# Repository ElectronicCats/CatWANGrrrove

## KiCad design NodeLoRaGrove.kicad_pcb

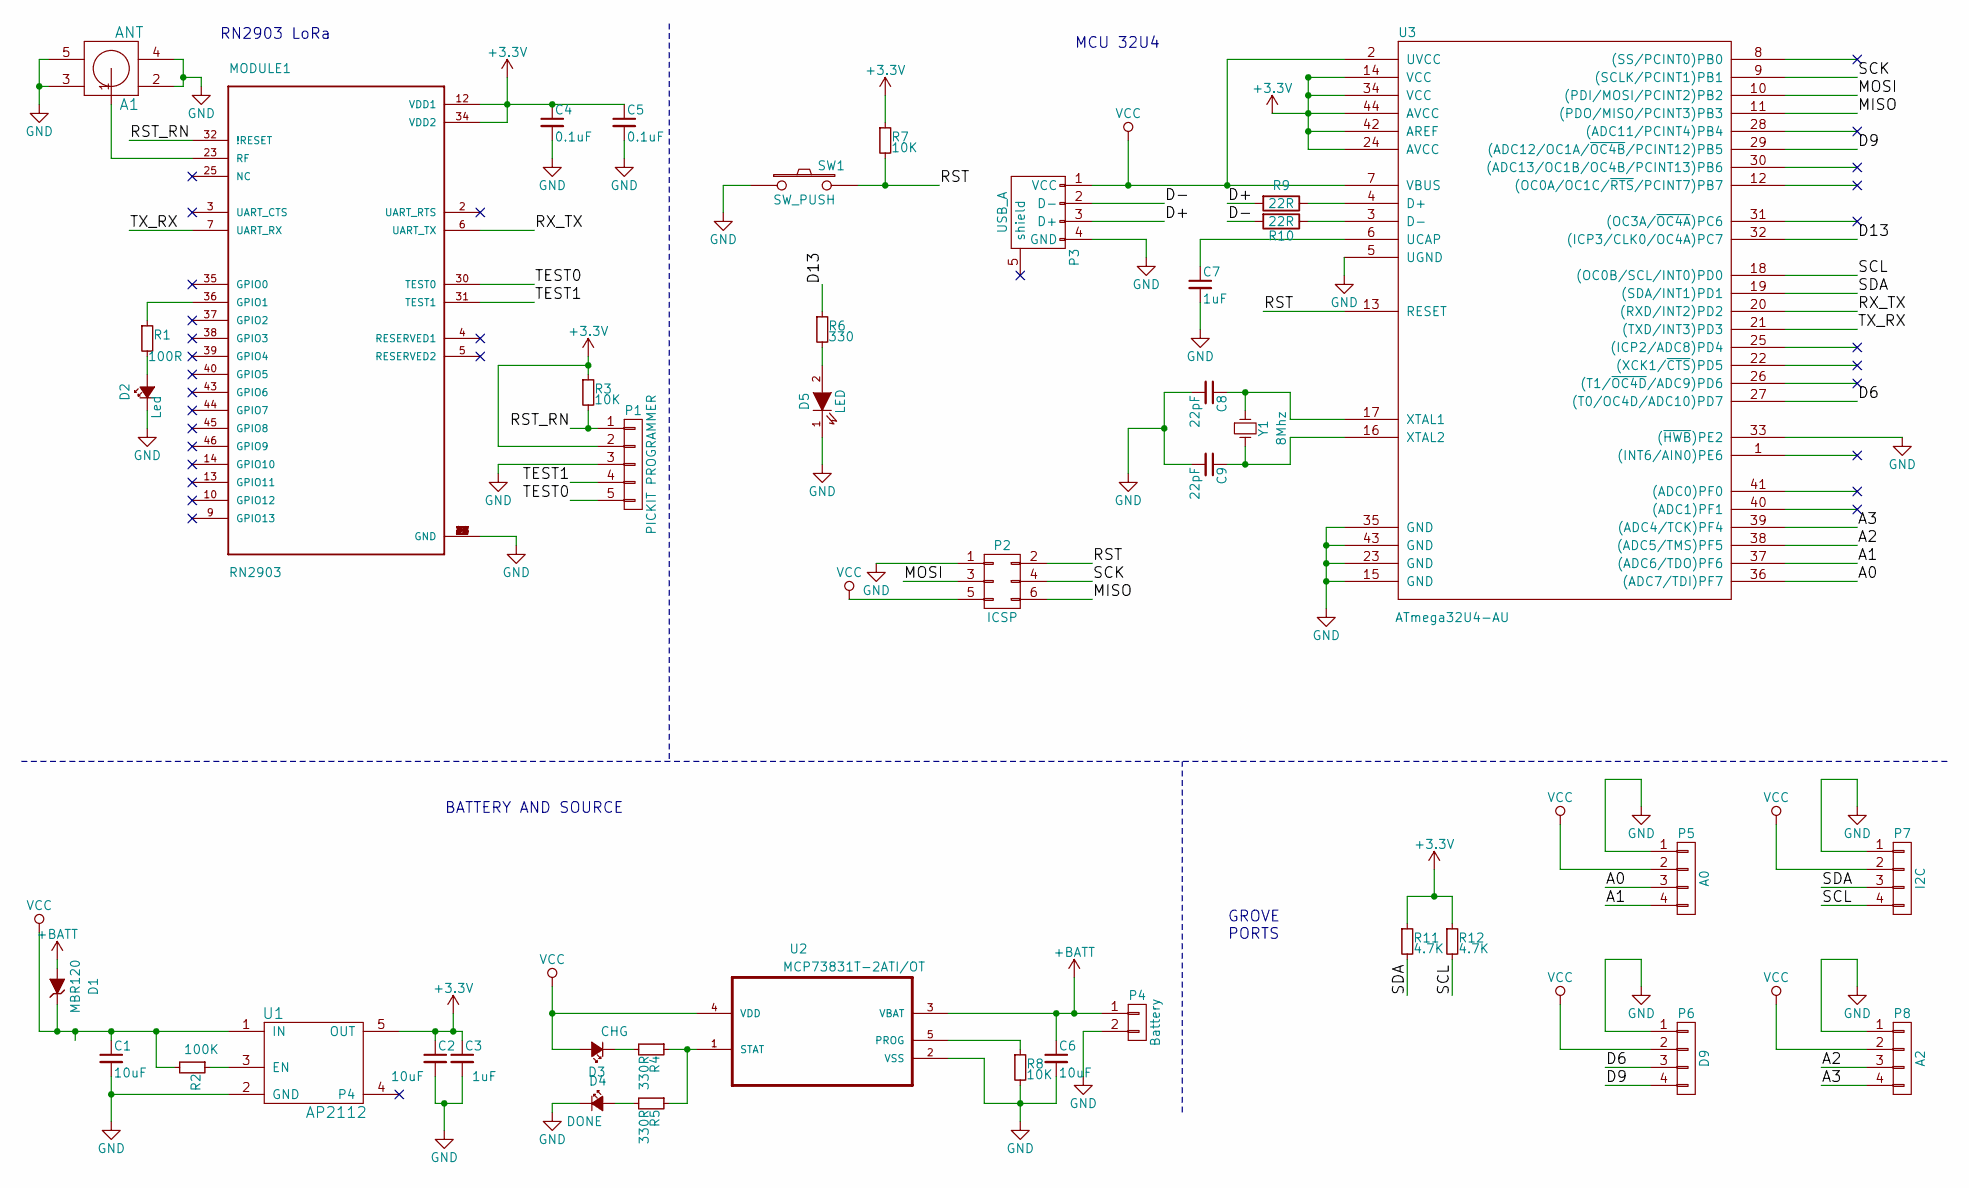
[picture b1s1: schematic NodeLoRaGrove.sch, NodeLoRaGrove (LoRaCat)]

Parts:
A1: ANT; GSG-SMA-EDGE
C1, C2, C6: 10uF; C_0805_HandSoldering
C3, C7: 1uF; C_0805_HandSoldering
C4, C5: 0.1uF; C_0805_HandSoldering
C8, C9: 22pF; C_0805_HandSoldering
D1: MBR120; SOD-123
D2: Led; LED_0805
D3: CHG; LED_0805
D4: DONE; LED_0805
D5: LED; LED_0805
MODULE1: RN2903; RN2483
P1: PICKIT PROGRAMMER; Pin_Header_Straight_1x05
P2: ICSP; Pin_Header_Straight_2x03
P3: USB_A; 10118192-0001LF
P4: Battery; Pin_Header_Straight_1x02
P5: A0; JST_PH_S4B-PH-K_04x2.00mm_Angled
P6: D9; JST_PH_S4B-PH-K_04x2.00mm_Angled
P7: I2C; JST_PH_S4B-PH-K_04x2.00mm_Angled
P8: A2; JST_PH_S4B-PH-K_04x2.00mm_Angled
R1: 100R; R_0805_HandSoldering
R2: 100K; R_0805_HandSoldering
R3, R7, R8: 10K; R_0805_HandSoldering
R4, R5: 330R; R_0805_HandSoldering
R6: 330; R_0805_HandSoldering
R9, R10: 22R; R_0805_HandSoldering
R11, R12: 4.7K; R_0805_HandSoldering
SW1: SW_PUSH; SW_SPST_KMR2
U1: AP2112; SOT-23-5
U2: MCP73831T-2ATI/OT; SOT-23-5
U3: ATmega32U4-AU; TQFP-44_10x10mm_Pitch0.8mm
Y1: 8Mhz; Crystal_HC49-SD_SMD

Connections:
+3V3: C2.1, C3.1, C4.1, C5.1, MODULE1.12 (VDD1), MODULE1.34 (VDD2), P1.2, R3.1, R7.1, R11.1, R12.1, U1.5 (OUT), U3.14 (VCC), U3.24 (AVCC), U3.34 (VCC), U3.42 (AREF), U3.44 (AVCC); also elsewhere on the board
+BATT: C6.1, D1.2 (A), P4.1, U2.3 (VBAT)
/A0: P5.3, U3.36 ((ADC7/TDI)PF7)
/A1: P5.4, U3.37 ((ADC6/TDO)PF6)
/A2: P8.3, U3.38 ((ADC5/TMS)PF5)
/A3: P8.4, U3.39 ((ADC4/TCK)PF4)
/D6: P6.3, U3.27 ((T0/OC4D/ADC10)PD7)
/D9: P6.4, U3.29 ((ADC12/OC1A/~OC4B~/PCINT12)PB5)
/D13: R6.1, U3.32 ((ICP3/CLK0/OC4A)PC7)
/D+: P3.3 (D+), R9.2
/D-: P3.2 (D-), R10.2
/MISO: P2.6, U3.11 ((PDO/MISO/PCINT3)PB3)
/MOSI: P2.3, U3.10 ((PDI/MOSI/PCINT2)PB2)
/RST: P2.2, R7.2, SW1.2, U3.13 (RESET)
/RST_RN: MODULE1.32 (!RESET), P1.1, R3.2; also elsewhere on the board
/RX_TX: MODULE1.6 (UART_TX), U3.20 ((RXD/INT2)PD2); also elsewhere on the board
/SCK: P2.4, U3.9 ((SCLK/PCINT1)PB1)
/SCL: P7.4, R12.2, U3.18 ((OC0B/SCL/INT0)PD0)
/SDA: P7.3, R11.2, U3.19 ((SDA/INT1)PD1)
/TEST0: MODULE1.30 (TEST0), P1.5; also elsewhere on the board
/TEST1: MODULE1.31 (TEST1), P1.4; also elsewhere on the board
/TX_RX: MODULE1.7 (UART_RX), U3.21 ((TXD/INT3)PD3); also elsewhere on the board
GND: A1.2, A1.3, A1.4, A1.5, C1.2, C2.2, C3.2, C4.2, C5.2, C6.2, C7.2, C8.2, C9.2, D2.1 (K), D4.1 (K), D5.1 (K), MODULE1.1 (GND), MODULE1.8 (GND), MODULE1.11 (GND), MODULE1.20 (GND), MODULE1.21 (GND), MODULE1.22 (GND), MODULE1.24 (GND), MODULE1.26 (GND), MODULE1.27 (GND), MODULE1.28 (GND), MODULE1.33 (GND), MODULE1.41 (GND), MODULE1.47 (GND), P1.3, P2.1, P3.4 (GND), P4.2, P5.1, P6.1, P7.1, P8.1, R8.2, SW1.1, U1.2 (GND), U2.2 (VSS), U3.5 (UGND), U3.15 (GND), U3.23 (GND), U3.33 ((~HWB~)PE2), U3.35 (GND), U3.43 (GND); also elsewhere on the board
unnamed 23: A1.1, MODULE1.23 (RF); also elsewhere on the board
unnamed: C7.1, U3.6 (UCAP)
unnamed: C8.1, U3.17 (XTAL1), Y1.1
unnamed: C9.1, U3.16 (XTAL2), Y1.2
unnamed: D2.2 (A), R1.2
unnamed: D3.1 (K), R4.2
unnamed: D4.2 (A), R5.2
unnamed: D5.2 (A), R6.2
unnamed 41: MODULE1.36 (GPIO1), R1.1; also elsewhere on the board
unnamed: R2.1, U1.3 (EN)
unnamed: R4.1, R5.1, U2.1 (STAT)
unnamed: R8.1, U2.5 (PROG)
unnamed: R9.1, U3.4 (D+)
unnamed: R10.1, U3.3 (D-)
VCC: C1.1, D1.1 (K), D3.2 (A), P2.5, P3.1 (VCC), P5.2, P6.2, P7.2, P8.2, R2.2, U1.1 (IN), U2.4 (VDD), U3.2 (UVCC), U3.7 (VBUS)

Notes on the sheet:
RN2903 LoRa
MCU 32U4
GROVE PORTS
BATTERY AND SOURCE

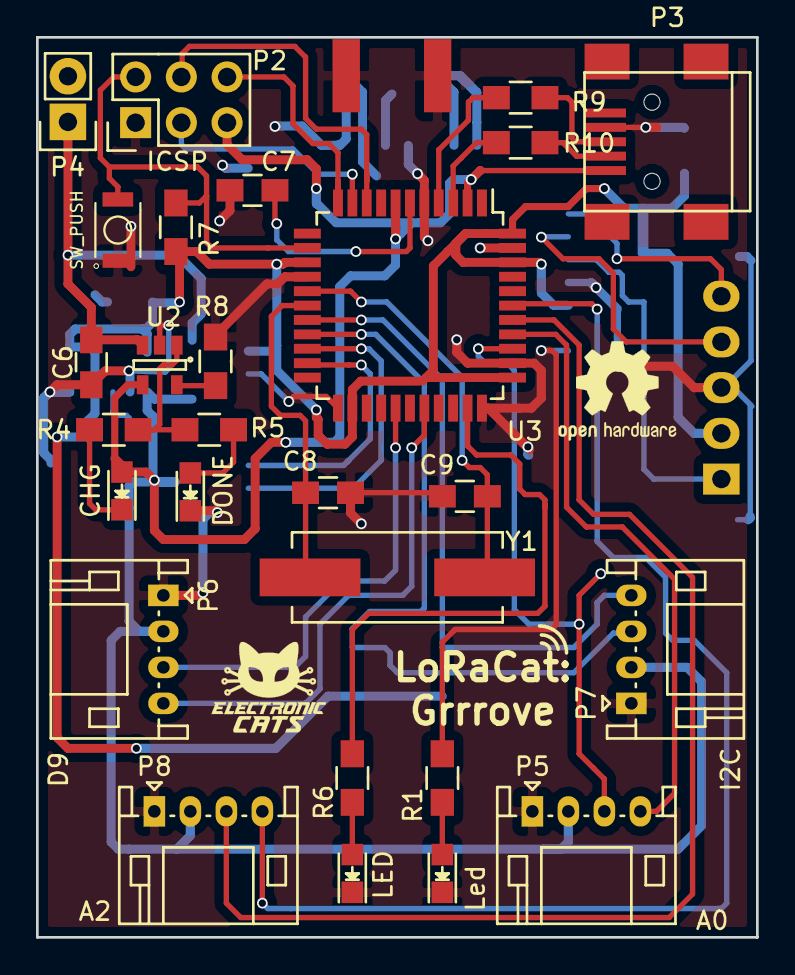
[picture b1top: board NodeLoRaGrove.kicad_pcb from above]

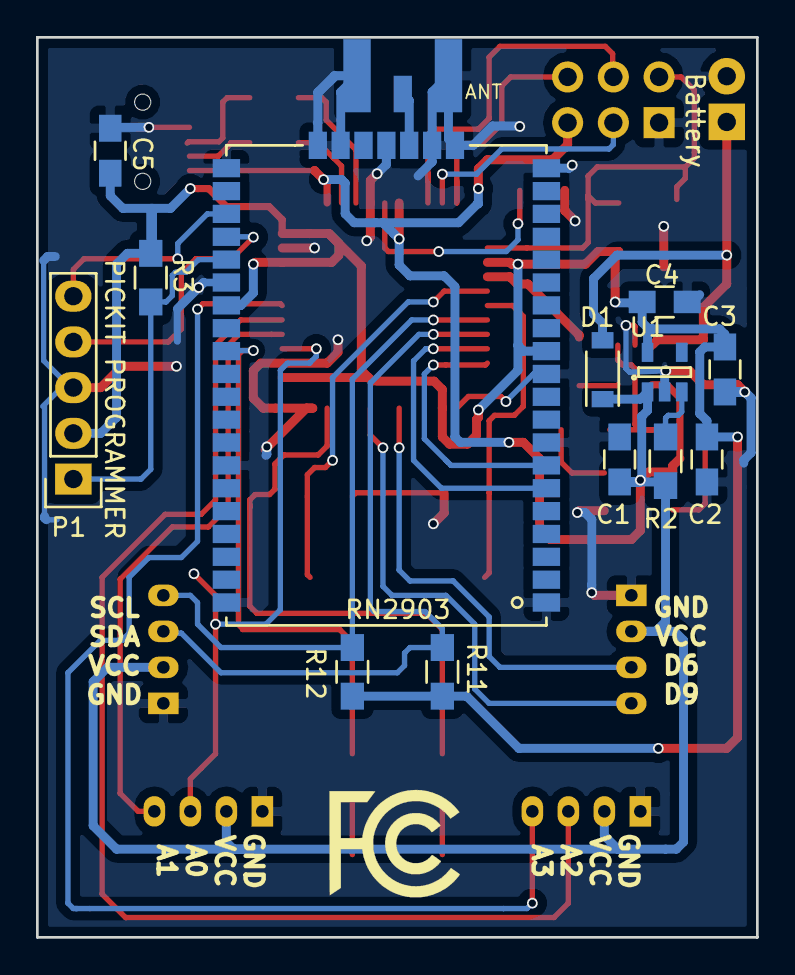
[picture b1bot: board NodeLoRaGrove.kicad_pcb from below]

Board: 2 copper layers, 40.0 x 50.0 mm, 41 parts (14 on the bottom side), 38 nets.

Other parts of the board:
RN2903: RN2903; RN2483

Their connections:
+3V3: RN2903.12, RN2903.34; also elsewhere on the board
/RST_RN: RN2903.32; also elsewhere on the board
/RX_TX: RN2903.6; also elsewhere on the board
/TEST0: RN2903.30; also elsewhere on the board
/TEST1: RN2903.31; also elsewhere on the board
/TX_RX: RN2903.7; also elsewhere on the board
GND: RN2903.1, RN2903.8, RN2903.11, RN2903.20, RN2903.21, RN2903.22, RN2903.24, RN2903.26, RN2903.27, RN2903.28, RN2903.33, RN2903.41, RN2903.47; also elsewhere on the board
unnamed 23: RN2903.23; also elsewhere on the board
unnamed 41: RN2903.36; also elsewhere on the board

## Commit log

2016-09-10 Schematic v0.1b
2016-09-10 Added gitignore
2016-09-10 added cache lib
2016-09-30 Update footprint and lib
2016-09-30 Update schematic
2016-09-30 Init PCB
2016-10-02 Add PCB 0.8v
2016-10-03 Update labels and added logo ElectronicCats
2016-10-18 Update Schematic remove leds
    Notes and leds remove
2016-11-24 Added PDF Squematic
2016-12-06 Added PCB 0.9v
2016-12-06 Added logos and change button
2016-12-06 Check DRC PCB
2016-12-15 Change USB connector
2017-01-03 Update logos
2017-01-04 Some vias and tracks fix
2017-01-04 Add ondas mamalonas
2017-01-04 Changed USB
2017-01-04 Fix Skilcreen
2017-01-12 added bom
2017-01-12 change gitignore ass csv
